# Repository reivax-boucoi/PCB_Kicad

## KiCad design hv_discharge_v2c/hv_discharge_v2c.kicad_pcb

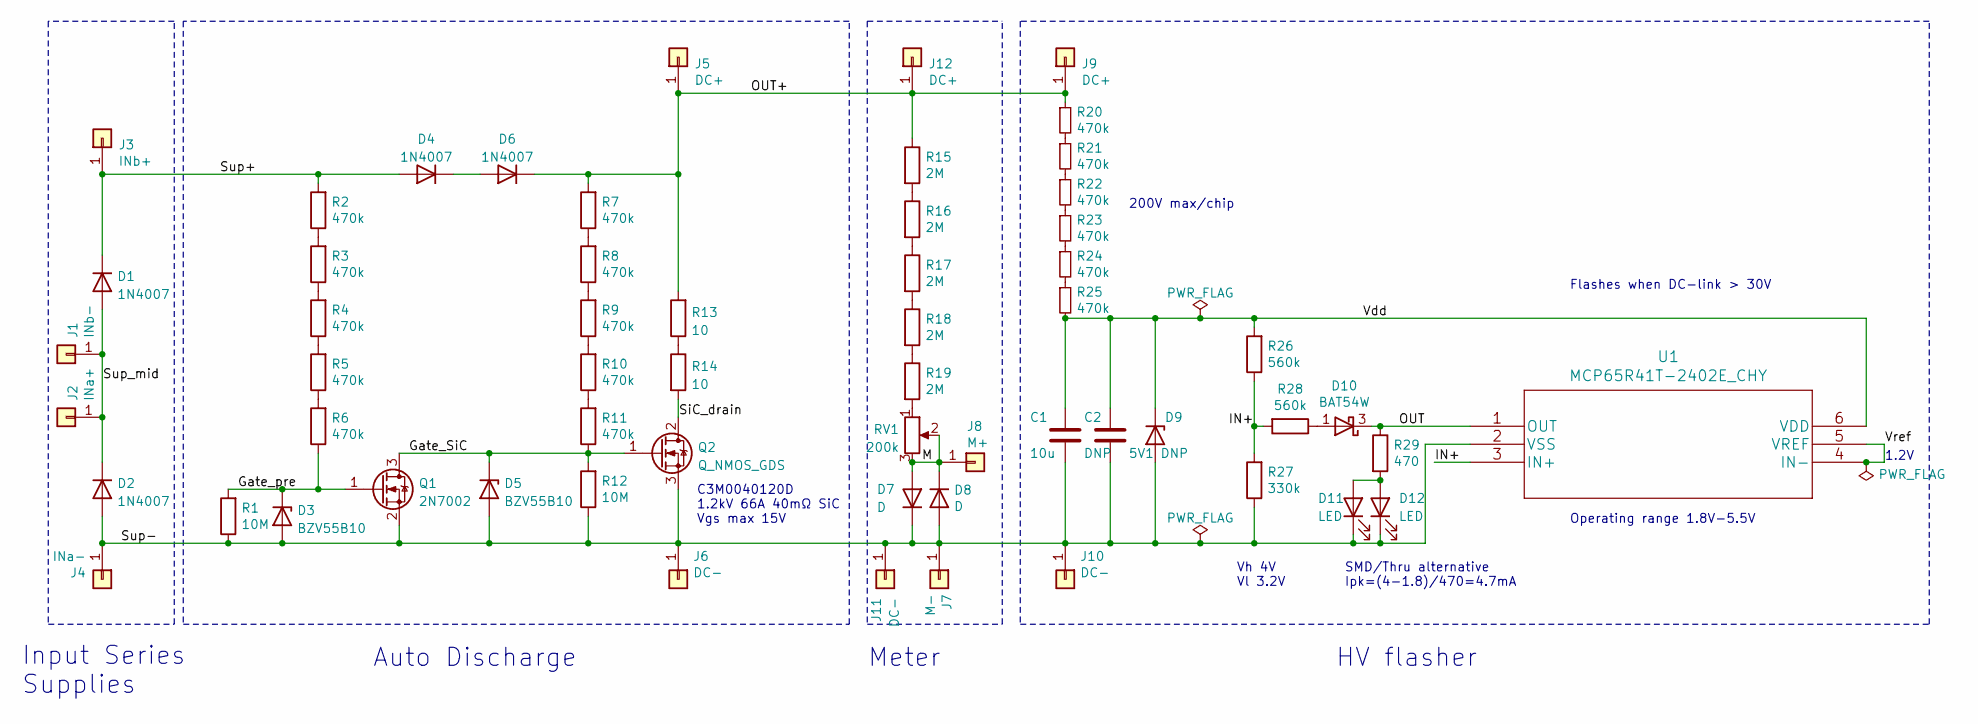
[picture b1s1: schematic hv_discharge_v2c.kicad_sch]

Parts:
C1: 10u; C_0805_2012Metric_Pad1.18x1.45mm_HandSolder
C2: DNP; C_0805_2012Metric_Pad1.18x1.45mm_HandSolder
D1, D2, D4, D6: 1N4007; D_DO-41_SOD81_P10.16mm_Horizontal
D3, D5: BZV55B10; D_MiniMELF
D7, D8: D; D_MiniMELF
D9: 5V1 DNP; D_MiniMELF
D10: BAT54W; SOT-23
D11: LED; LED_0805_2012Metric_Pad1.15x1.40mm_HandSolder
D12: LED; LED_D5.0mm
J1: INb-; TestPoint_THTPad_D2.5mm_Drill1.2mm
J2: INa+; TestPoint_THTPad_D2.5mm_Drill1.2mm
J3: INb+; TestPoint_THTPad_D2.5mm_Drill1.2mm
J4: INa-; TestPoint_THTPad_D2.5mm_Drill1.2mm
J5, J9, J12: DC+; TestPoint_THTPad_D2.5mm_Drill1.2mm
J6, J10, J11: DC-; TestPoint_THTPad_D2.5mm_Drill1.2mm
J7: M-; TestPoint_THTPad_D2.5mm_Drill1.2mm
J8: M+; TestPoint_THTPad_D2.5mm_Drill1.2mm
Q1: 2N7002; SOT-23
Q2: Q_NMOS_GDS; TO-247-3_Vertical
R1, R12: 10M; R_0805_2012Metric_Pad1.20x1.40mm_HandSolder
R2, R3, R4, R5, R6, R7, R8, R9, R10, R11, R20, R21, R22, R23, R24, R25: 470k; R_0805_2012Metric_Pad1.20x1.40mm_HandSolder
R13, R14: 10; THS2510RJ_special
R15, R16, R17, R18, R19: 2M; R_0805_2012Metric_Pad1.20x1.40mm_HandSolder
R26, R28: 560k; R_0805_2012Metric_Pad1.20x1.40mm_HandSolder
R27: 330k; R_0805_2012Metric_Pad1.20x1.40mm_HandSolder
R29: 470; R_0805_2012Metric_Pad1.20x1.40mm_HandSolder
RV1: 200k; Potentiometer_Bourns_3266Y_Vertical
U1: MCP65R41T-2402E_CHY; MCP65R41T-2402E

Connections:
/Gate_SiC: D5.1 (K), Q1.3 (D), Q2.1 (G), R11.1, R12.2
/Gate_pre: D3.1 (K), Q1.1 (G), R1.2, R6.1
/IN+: R26.1, R27.2, R28.2, U1.3 (IN+)
/M: D7.2 (A), D8.1 (K), J8.1, RV1.2, RV1.3
/OUT: D10.3 (K), R29.1, U1.1 (OUT)
/OUT+: D6.1 (K), J5.1, J9.1, J12.1, R7.2, R13.2, R15.1, R20.1
/SiC_drain: Q2.2 (D), R14.2
/Sup+: D1.1 (K), D4.2 (A), J3.1, R2.2
/Sup-: C1.2, C2.2, D2.2 (A), D3.2 (A), D5.2 (A), D7.1 (K), D8.2 (A), D9.2 (A), D11.1 (K), D12.1 (K), J4.1, J6.1, J7.1, J10.1, J11.1, Q1.2 (S), Q2.3 (S), R1.1, R12.1, R27.1, U1.2 (VSS)
/Sup_mid: D1.2 (A), D2.1 (K), J1.1, J2.1
/Vdd: C1.1, C2.1, D9.1 (K), R25.2, R26.2, U1.6 (VDD)
/Vref: U1.4 (IN-), U1.5 (VREF)
unnamed: D4.1 (K), D6.2 (A)
unnamed: D11.2 (A), D12.2 (A), R29.2
unnamed: R2.1, R3.2
unnamed: R3.1, R4.2
unnamed: R4.1, R5.2
unnamed: R5.1, R6.2
unnamed: R7.1, R8.2
unnamed: R8.1, R9.2
unnamed: R10.1, R11.2
unnamed: R9.1, R10.2
unnamed: R15.2, R16.1
unnamed: R16.2, R17.1
unnamed: R17.2, R18.1
unnamed: R18.2, R19.1
unnamed: R19.2, RV1.1
unnamed: R20.2, R21.1
unnamed: R21.2, R22.1
unnamed: R22.2, R23.1
unnamed: R23.2, R24.1
unnamed: R24.2, R25.1
unnamed: D10.1 (A), R28.1

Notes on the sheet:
Input Series Supplies
1.2V
Meter
Flashes when DC-link > 30V
SMD/Thru alternative Ipk=(4-1.8)/470=4.7mA
C3M0040120D 1.2kV 66A 40mΩ SiC Vgs max 15V
HV flasher
Auto Discharge
Operating range 1.8V-5.5V
Vh 4V Vl 3.2V
200V max/chip

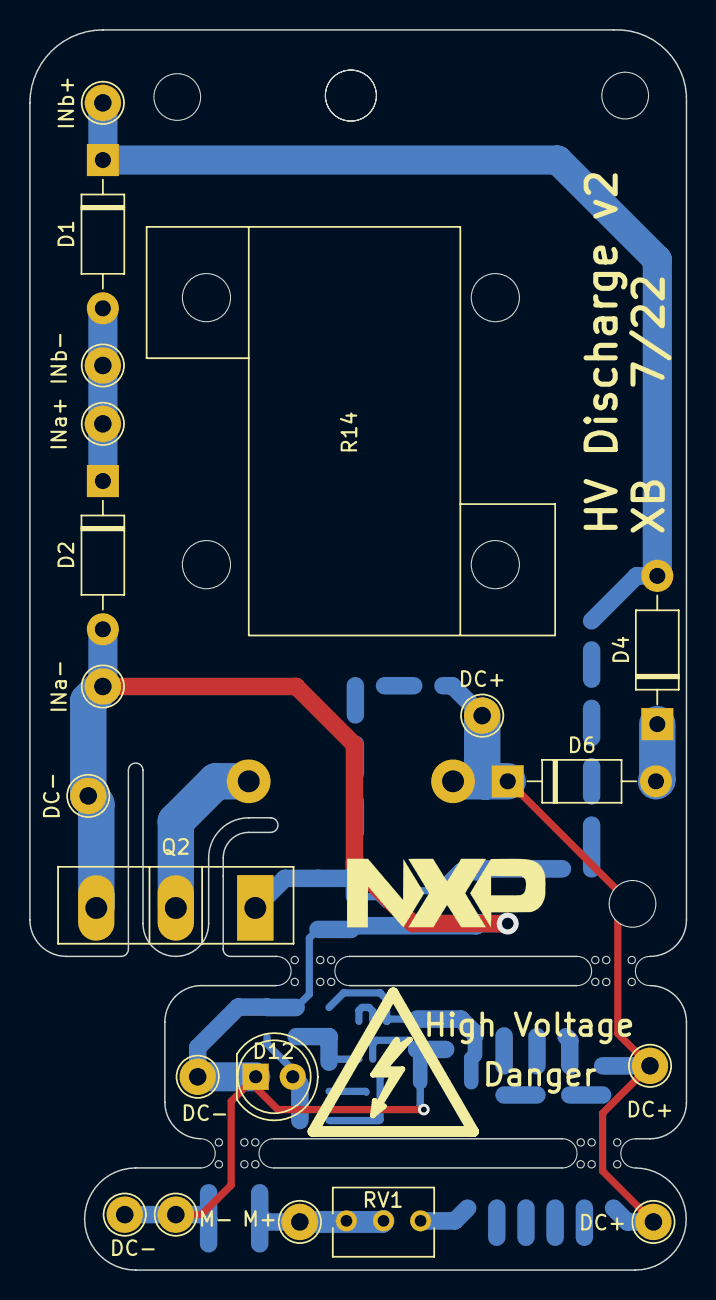
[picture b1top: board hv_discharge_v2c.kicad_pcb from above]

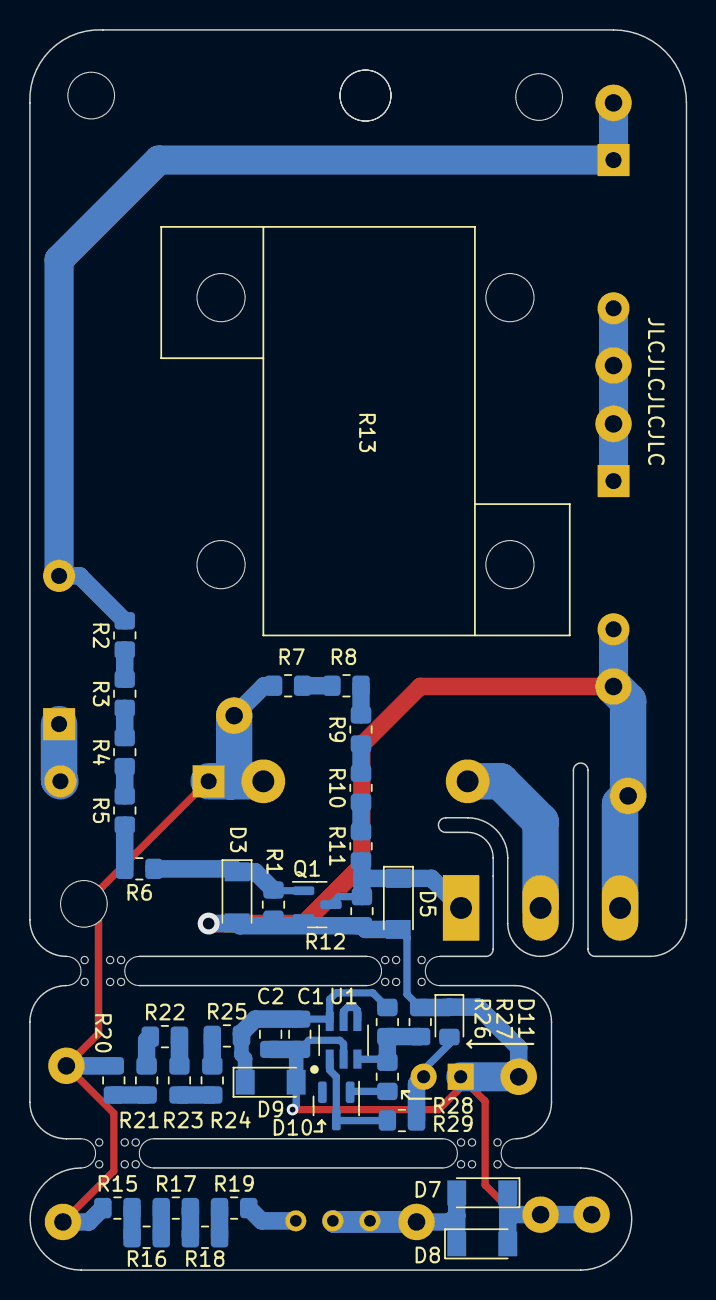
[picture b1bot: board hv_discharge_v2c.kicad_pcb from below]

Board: 2 copper layers, 45.0 x 85.0 mm, 63 parts (39 on the bottom side), 33 nets.

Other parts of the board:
mouse-bite-2mm-slot, mouse-bite-2mm-slot#2, mouse-bite-2mm-slot#3, mouse-bite-2mm-slot#4: VAL**; mouse-bite-2mm-slot

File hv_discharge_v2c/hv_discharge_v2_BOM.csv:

Reference,Value,Footprint,Datasheet,Qty,DNP
C1,10u,Capacitor_SMD:C_0805_2012Metric_Pad1.18x1.45mm_HandSolder,~,1,
C2,DNP,Capacitor_SMD:C_0805_2012Metric_Pad1.18x1.45mm_HandSolder,~,1,x
"D1,D2,D4,D6",1N4007,Diode_THT:D_DO-41_SOD81_P10.16mm_Horizontal,http://www.vishay.com/docs/88503/1n4001.pdf,4,"D1/D2 DNP, diode supplied replaces both D4/D6"
"D3,D5",BZV55B10,Diode_SMD:D_MiniMELF,https://assets.nexperia.com/documents/data-sheet/BZV55_SER.pdf,2,
"D7,D8",D,Diode_SMD:D_MiniMELF,~,2,x
D9,5V1,Diode_SMD:D_MiniMELF,~,1,
D10,BAT54W,Package_TO_SOT_SMD:SOT-23,https://assets.nexperia.com/documents/data-sheet/BAT54W_SER.pdf,1,
D11,LED,LED_SMD:LED_0805_2012Metric_Pad1.15x1.40mm_HandSolder,~,1,x
D12,LED,LED_THT:LED_D5.0mm,~,1,
J1,INb-,TestPoint:TestPoint_THTPad_D2.5mm_Drill1.2mm,~,1,x
J2,INa+,TestPoint:TestPoint_THTPad_D2.5mm_Drill1.2mm,~,1,x
J3,INb+,TestPoint:TestPoint_THTPad_D2.5mm_Drill1.2mm,~,1,x
J4,INa-,TestPoint:TestPoint_THTPad_D2.5mm_Drill1.2mm,~,1,x
"J5,J9,J12",DC+,TestPoint:TestPoint_THTPad_D2.5mm_Drill1.2mm,~,3,x
"J6,J10,J11",DC-,TestPoint:TestPoint_THTPad_D2.5mm_Drill1.2mm,~,3,x
J7,M-,TestPoint:TestPoint_THTPad_D2.5mm_Drill1.2mm,~,1,x
J8,M+,TestPoint:TestPoint_THTPad_D2.5mm_Drill1.2mm,~,1,x
Q1,2N7002,Package_TO_SOT_SMD:SOT-23,https://www.onsemi.com/pub/Collateral/NDS7002A-D.PDF,1,
Q2,Q_NMOS_GDS,Package_TO_SOT_THT:TO-247-3_Vertical,~,1,supplied
"R1,R12",10M,Resistor_SMD:R_0805_2012Metric_Pad1.20x1.40mm_HandSolder,~,2,
"R2,R3,R4,R5,R6,R7,R8,R9,R10,R11,R20,R21,R22,R23,R24,R25",470k,Resistor_SMD:R_0805_2012Metric_Pad1.20x1.40mm_HandSolder,~,16,
"R13,R14",10,footprints:THS2510RJ_special,~,2,supplied 47R
"R15,R16,R17,R18,R19",2M,Resistor_SMD:R_0805_2012Metric_Pad1.20x1.40mm_HandSolder,~,5,x
"R26,R28",560k,Resistor_SMD:R_0805_2012Metric_Pad1.20x1.40mm_HandSolder,~,2,
R27,330k,Resistor_SMD:R_0805_2012Metric_Pad1.20x1.40mm_HandSolder,~,1,
R29,470,Resistor_SMD:R_0805_2012Metric_Pad1.20x1.40mm_HandSolder,~,1,
RV1,200k,Potentiometer_THT:Potentiometer_Bourns_3266Y_Vertical,~,1,x
U1,MCP65R41T-2402E_CHY,footprints:MCP65R41T-2402E,,1,

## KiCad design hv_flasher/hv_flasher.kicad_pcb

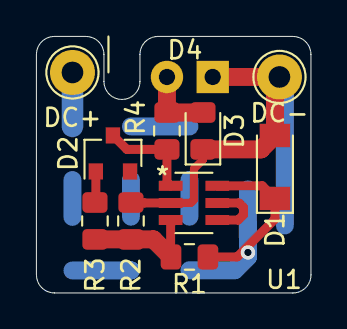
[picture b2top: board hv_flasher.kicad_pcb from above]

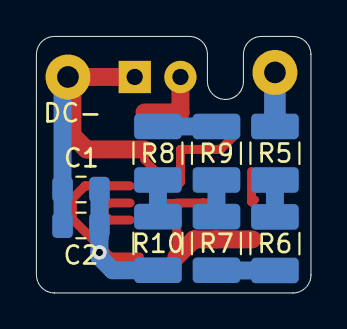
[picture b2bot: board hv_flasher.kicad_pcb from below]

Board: 2 copper layers, 15.2 x 14.2 mm, 19 parts (8 on the bottom side), 13 nets.

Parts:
C1, C2: 10u; C_0805_2012Metric_Pad1.15x1.40mm_HandSolder
D1: D_Zener; D_MiniMELF
D2: BAT54W; SOT-23
D3: LED; LED_0805_2012Metric_Pad1.15x1.40mm_HandSolder
D4: LED; LED_D5.0mm
DC+: DC+; TestPoint_THTPad_D2.5mm_Drill1.2mm
DC-: DC-; TestPoint_THTPad_D2.5mm_Drill1.2mm
R1, R2, R3: 100k; R_0805_2012Metric_Pad1.15x1.40mm_HandSolder
R4: 1k; R_0805_2012Metric_Pad1.15x1.40mm_HandSolder
R5, R6, R7, R8, R9, R10: 100k; R_1210_3225Metric_Pad1.42x2.65mm_HandSolder
U1: MCP65R41T-2402E_CHY; MCP65R41T-2402E

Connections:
/IN+: R1.1, R2.2, R3.2, U1.3
/OUT: D2.3, R4.1, U1.1
/Vdd: C1.1, C2.1, D1.1, R1.2, R10.2, U1.6
/Vref: U1.4, U1.5
/Vss: C1.2, C2.2, D1.2, D3.1, D4.1, DC-.1, R2.1, U1.2
unnamed: D2.1, R3.1
unnamed: D3.2, D4.2, R4.2
unnamed: DC+.1, R5.1
unnamed: R5.2, R6.1
unnamed: R6.2, R7.1
unnamed: R7.2, R8.1
unnamed: R8.2, R9.1
unnamed: R9.2, R10.1

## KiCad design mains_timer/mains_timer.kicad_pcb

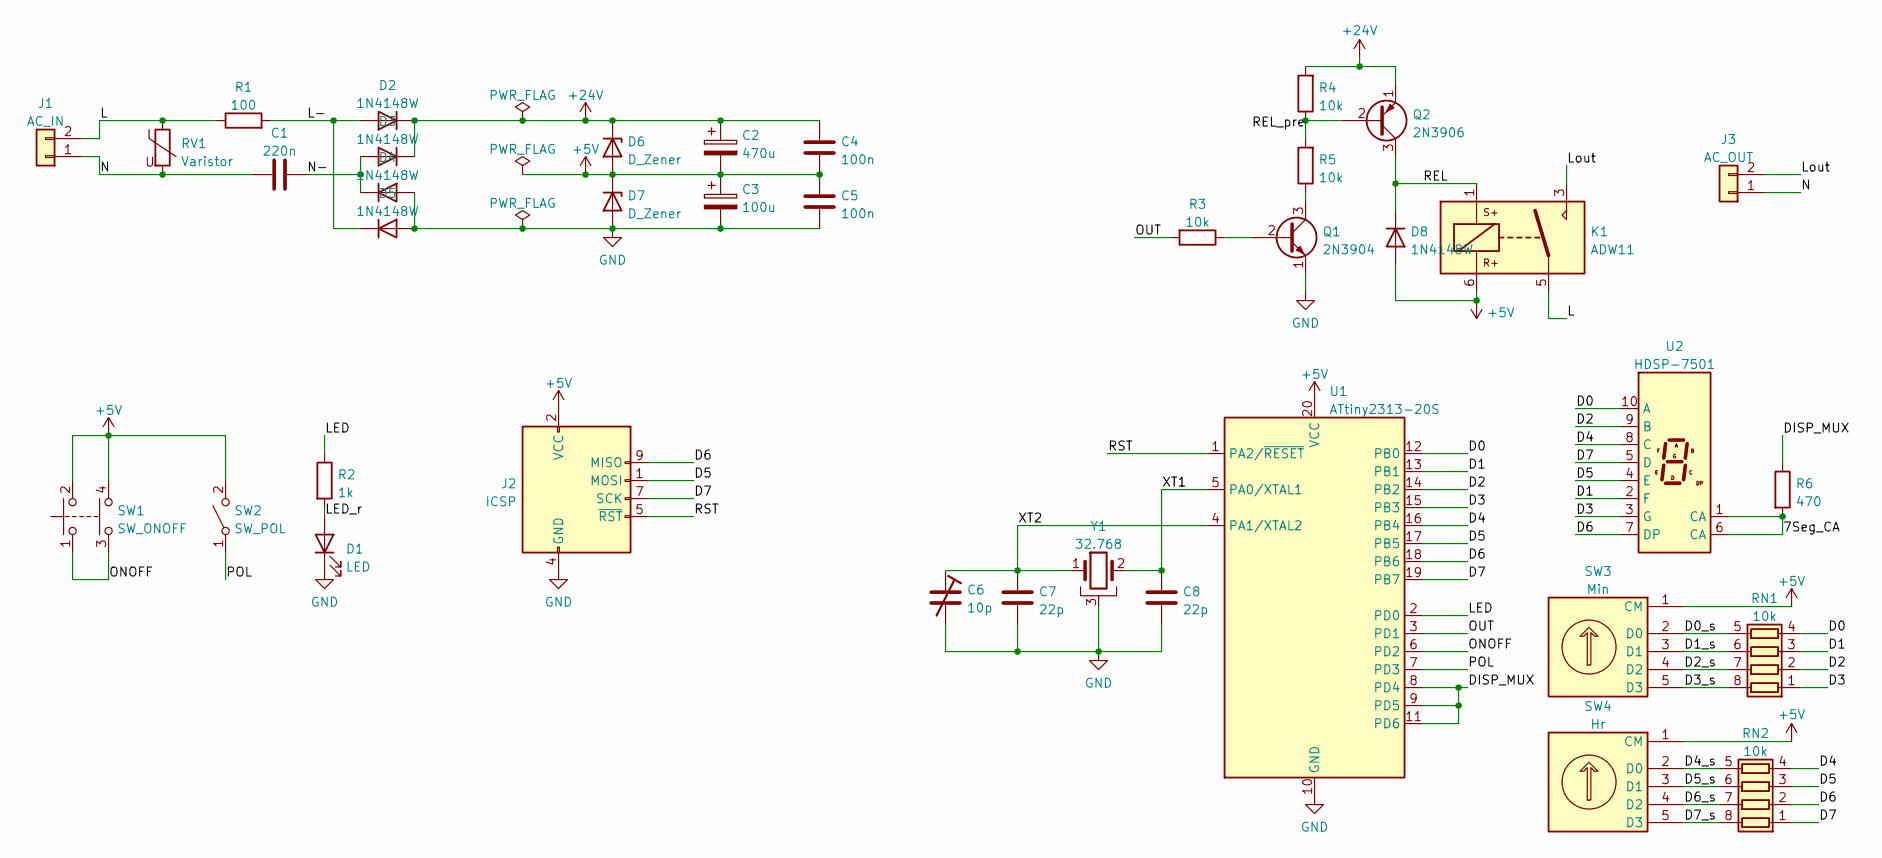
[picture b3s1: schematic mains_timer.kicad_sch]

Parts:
C1: 220n; C_Rect_L26.5mm_W8.5mm_P22.50mm_MKS4
C2: 470u; CP_Radial_D10.0mm_P2.50mm_P5.00mm
C3: 100u; CP_Radial_D7.5mm_P2.50mm
C4, C5: 100n; C_0603_1608Metric_Pad1.08x0.95mm_HandSolder
C6: 10p
C7, C8: 22p; C_0603_1608Metric_Pad1.08x0.95mm_HandSolder
D1: LED; LED_D5.0mm
D2, D3, D4, D5, D8: 1N4148W; D_SOD-123
D6: D_Zener; D_DO-15_P3.81mm_Vertical_AnodeUp
D7: D_Zener; D_MELF
J1: AC_IN; TerminalBlock_bornier-2_P5.08mm
J2: ICSP; PinHeader_2x05_P2.54mm_Vertical
J3: AC_OUT; TerminalBlock_bornier-2_P5.08mm
K1: ADW11; Relay_1P1T_NO_10x24x18.8mm_Panasonic_ADW11xxxxW_THT
Q1: 2N3904; TO-92_Inline
Q2: 2N3906; TO-92_Inline
R1: 100; R_Axial_DIN0309_L9.0mm_D3.2mm_P2.54mm_Vertical
R2: 1k; R_0603_1608Metric_Pad0.98x0.95mm_HandSolder
R3, R4, R5: 10k; R_0603_1608Metric_Pad0.98x0.95mm_HandSolder
R6: 470; R_0603_1608Metric_Pad0.98x0.95mm_HandSolder
RN1, RN2: 10k; R_Array_Concave_4x0603
RV1: Varistor; RV_Disc_D12mm_W4.6mm_P7.5mm
SW1: SW_ONOFF; Push_E-Switch_KS01Q01
SW2: SW_POL; PinHeader_1x02_P2.54mm_Vertical
SW3: Min; PinHeader_1x05_P2.54mm_Vertical
SW4: Hr; PinHeader_1x05_P2.54mm_Vertical
U1: ATtiny2313-20S; SOIC-20W_7.5x12.8mm_P1.27mm
U2: HDSP-7501; HDSP-A151
Y1: 32.768; Crystal_C38-LF_D3.0mm_L8.0mm_Horizontal_1EP_style2

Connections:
+5V: C2.2, C3.1, C4.2, C5.1, D6.2 (A), D7.1 (K), D8.2 (A), J2.2 (VCC), K1.6, SW1.2, SW1.4, SW2.2 (B), SW3.1 (CM), SW4.1 (CM), U1.20 (VCC)
+24V: C2.1, C4.1, D2.1 (K), D3.1 (K), D6.1 (K), Q2.1 (E), R4.2
/7Seg_CA: R6.2, U2.1 (CA), U2.6 (CA)
/D0: RN1.4 (R4.1), U1.12 (PB0), U2.10 (A)
/D0_s: RN1.5 (R4.2), SW3.2 (D0)
/D1: RN1.3 (R3.1), U1.13 (PB1), U2.2 (F)
/D1_s: RN1.6 (R3.2), SW3.3 (D1)
/D2: RN1.2 (R2.1), U1.14 (PB2), U2.9 (B)
/D2_s: RN1.7 (R2.2), SW3.4 (D2)
/D3: RN1.1 (R1.1), U1.15 (PB3), U2.3 (G)
/D3_s: RN1.8 (R1.2), SW3.5 (D3)
/D4: RN2.4 (R4.1), U1.16 (PB4), U2.8 (C)
/D4_s: RN2.5 (R4.2), SW4.2 (D0)
/D5: J2.1 (MOSI), RN2.3 (R3.1), U1.17 (PB5), U2.4 (E)
/D5_s: RN2.6 (R3.2), SW4.3 (D1)
/D6: J2.9 (MISO), RN2.2 (R2.1), U1.18 (PB6), U2.7 (DP)
/D6_s: RN2.7 (R2.2), SW4.4 (D2)
/D7: J2.7 (SCK), RN2.1 (R1.1), U1.19 (PB7), U2.5 (D)
/D7_s: RN2.8 (R1.2), SW4.5 (D3)
/DISP_MUX: R6.1, U1.8 (PD4), U1.9 (PD5), U1.11 (PD6)
/L: J1.2, K1.5, R1.1, RV1.1
/L-: D2.2 (A), D5.1 (K), R1.2
/LED: R2.1, U1.2 (PD0)
/LED_r: D1.2 (A), R2.2
/Lout: J3.2, K1.3
/N: C1.1, J1.1, J3.1, RV1.2
/N-: C1.2, D3.2 (A), D4.1 (K)
/ONOFF: SW1.1, SW1.3, U1.6 (PD2)
/OUT: R3.2, U1.3 (PD1)
/POL: SW2.1 (A), U1.7 (PD3)
/REL: D8.1 (K), K1.1, Q2.3 (C)
/REL_pre: Q2.2 (B), R4.1, R5.2
/RST: J2.5 (~RST), U1.1 (PA2/~RESET)
/XT1: C8.1, U1.5 (PA0/XTAL1), Y1.2
/XT2: C6.1, C7.1, U1.4 (PA1/XTAL2), Y1.1
GND: C3.2, C5.2, C6.2, C7.2, C8.2, D1.1 (K), D4.2 (A), D5.2 (A), D7.2 (A), J2.4 (GND), J2.6 (GND), J2.8 (GND), J2.10 (GND), Q1.1 (E), U1.10 (GND), Y1.3
unnamed: Q1.2 (B), R3.1
unnamed: Q1.3 (C), R5.1

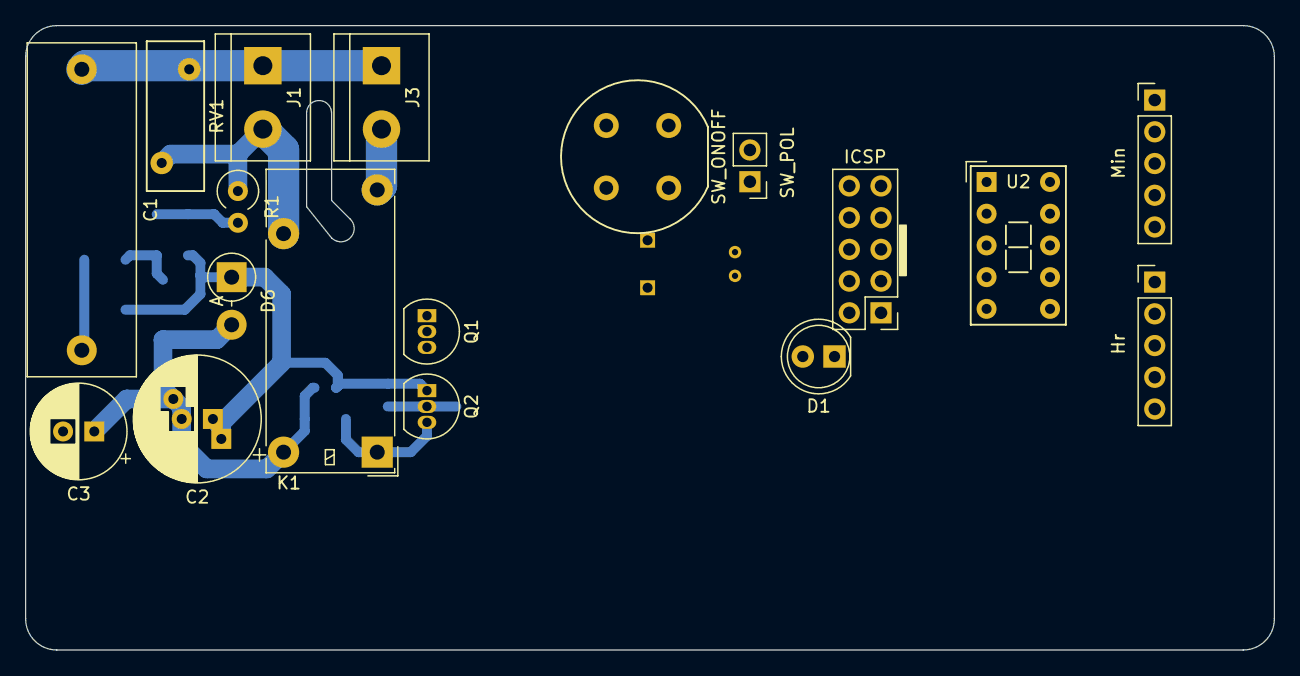
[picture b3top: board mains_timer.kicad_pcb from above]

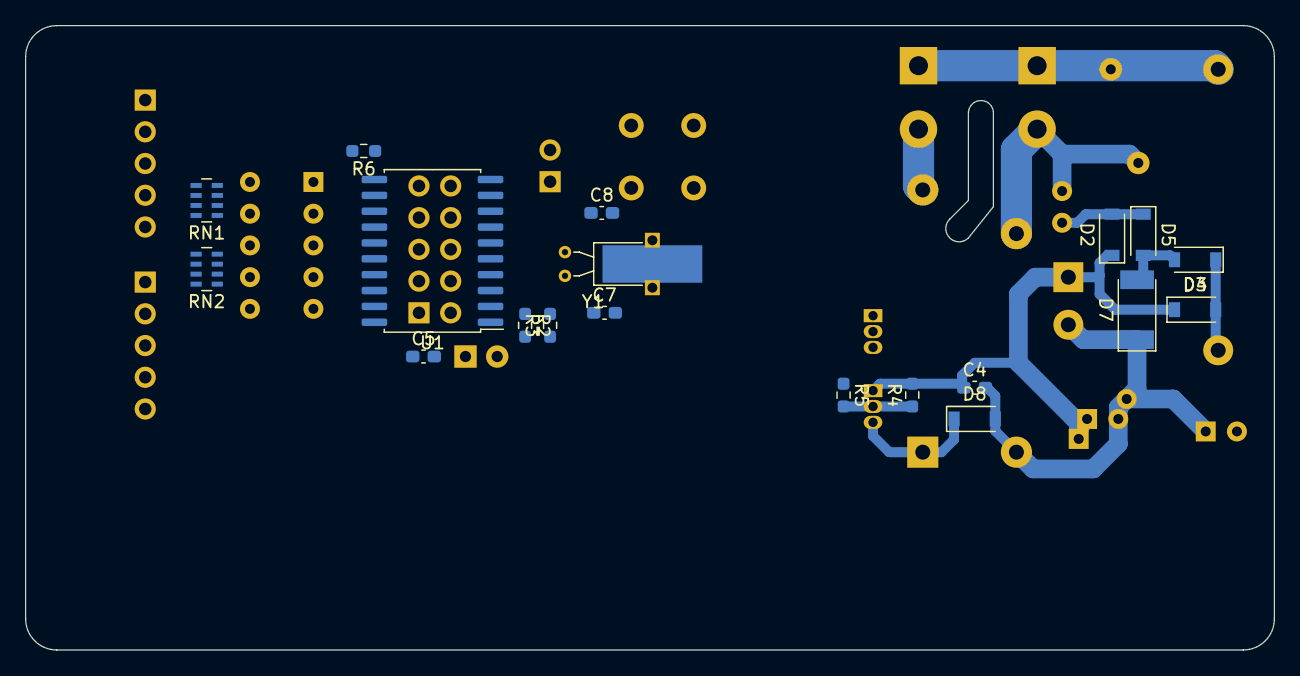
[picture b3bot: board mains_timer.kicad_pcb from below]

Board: 2 copper layers, 100.0 x 50.0 mm, 37 parts (19 on the bottom side), 38 nets.

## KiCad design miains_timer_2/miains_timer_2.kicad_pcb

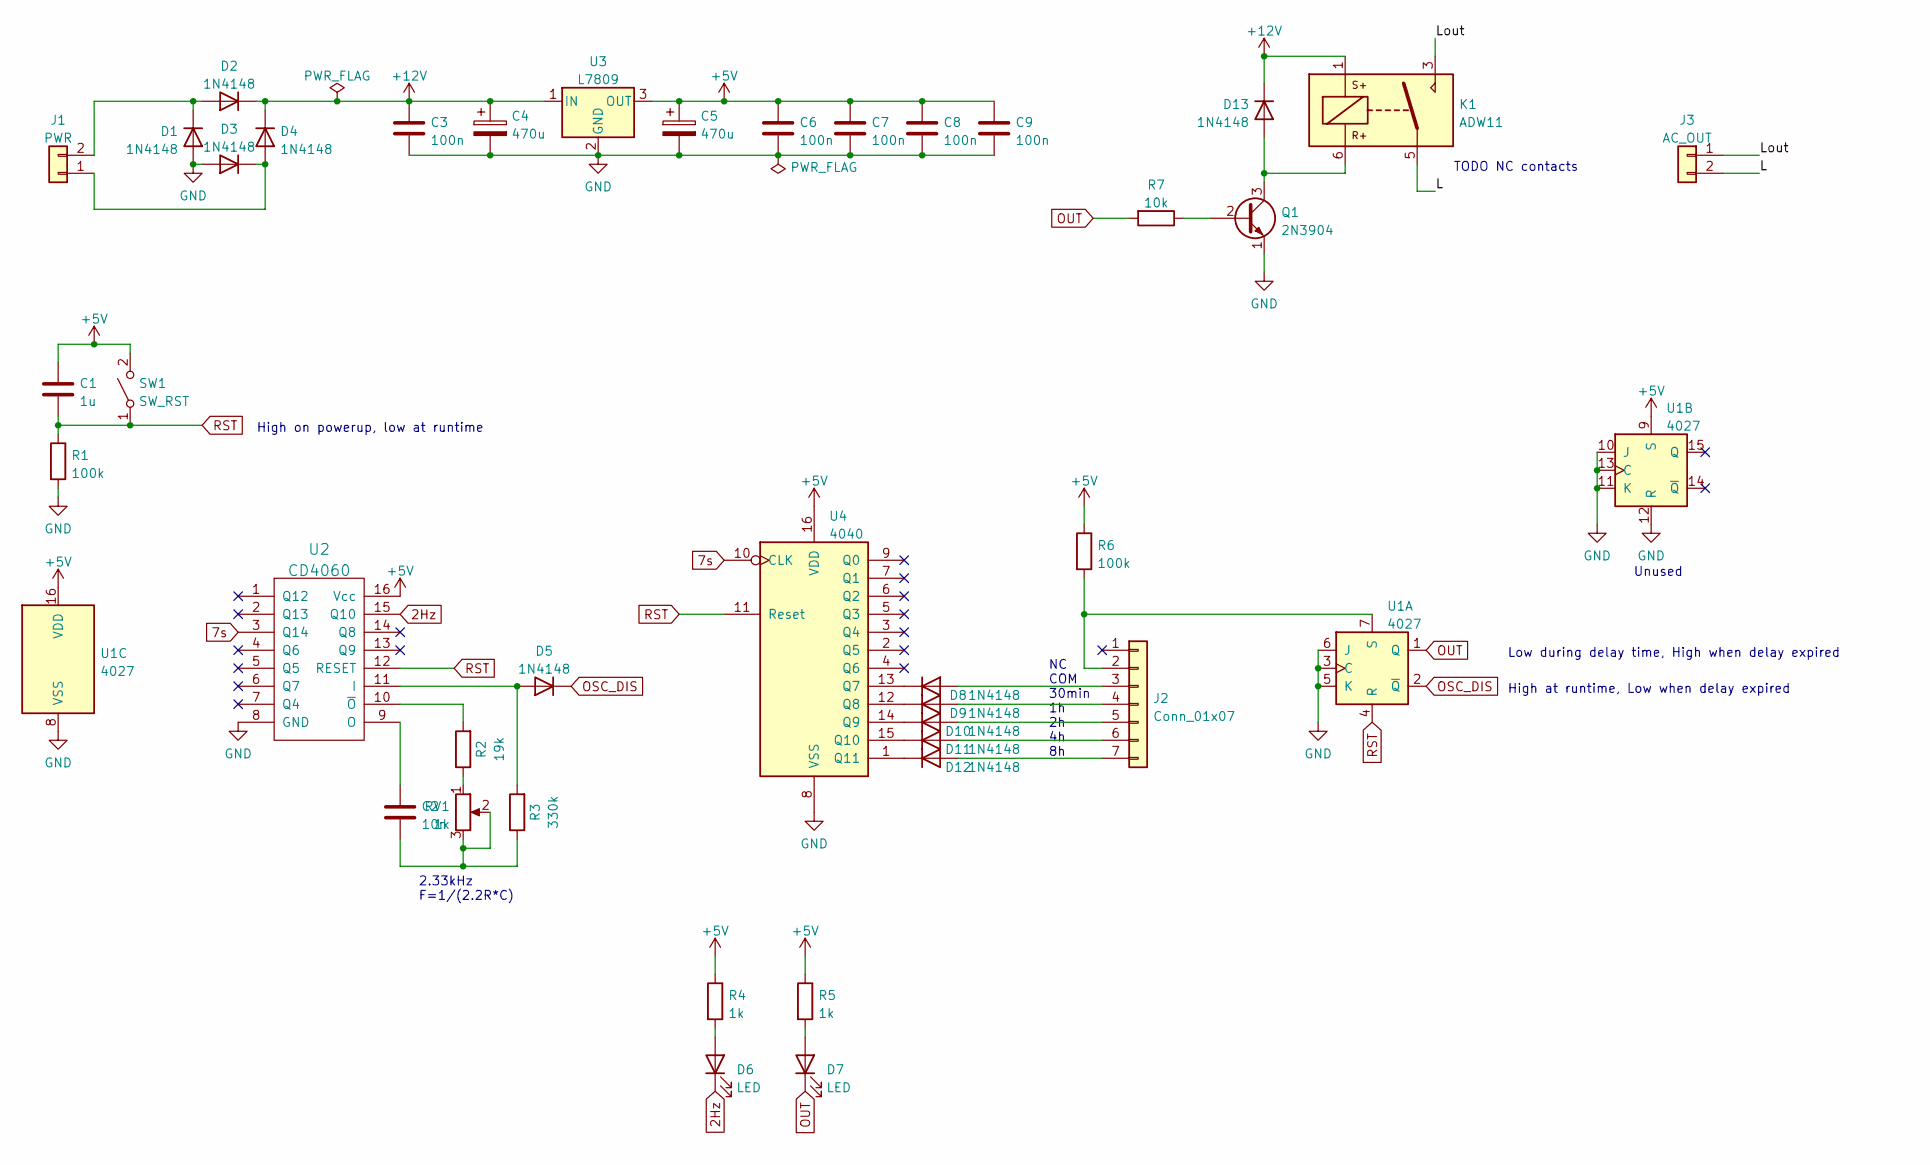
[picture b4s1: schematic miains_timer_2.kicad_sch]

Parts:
C1: 1u; C_0805_2012Metric_Pad1.18x1.45mm_HandSolder
C2: 10n; C_0805_2012Metric_Pad1.18x1.45mm_HandSolder
C3, C6, C7, C8, C9: 100n; C_0805_2012Metric_Pad1.18x1.45mm_HandSolder
C4, C5: 470u; CP_Radial_D8.0mm_P2.50mm
D1, D2, D3, D4, D5, D8, D9, D10, D11, D12, D13: 1N4148; D_MiniMELF
D6, D7: LED; LED_D5.0mm
J1: PWR; TerminalBlock_bornier-2_P5.08mm
J2: Conn_01x07; PinSocket_1x07_P2.54mm_Vertical
J3: AC_OUT; TerminalBlock_bornier-2_P5.08mm
K1: ADW11; Relay_1P1T_NO_10x24x18.8mm_Panasonic_ADW11xxxxW_THT
Q1: 2N3904; TO-92_Inline
R1, R6: 100k; R_0805_2012Metric_Pad1.20x1.40mm_HandSolder
R2: 19k; R_0805_2012Metric_Pad1.20x1.40mm_HandSolder
R3: 330k; R_0805_2012Metric_Pad1.20x1.40mm_HandSolder
R4, R5: 1k; R_0805_2012Metric_Pad1.20x1.40mm_HandSolder
R7: 10k; R_0805_2012Metric_Pad1.20x1.40mm_HandSolder
RV1: 1k; Potentiometer_Bourns_3386X_Horizontal
SW1: SW_RST; PinHeader_1x02_P2.54mm_Vertical
U1: 4027; DIP-16_W7.62mm_Socket_LongPads
U2: CD4060; DIP-16_W7.62mm_Socket_LongPads
U3: L7809; TO-220-3_Vertical
U4: 4040; DIP-16_W7.62mm_Socket_LongPads

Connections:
2Hz: D6.1 (K), U2.15 (Q10)
7s: U2.3 (Q14), U4.10 (CLK)
+5V: C1.1, C5.1, C6.1, C7.1, C8.1, C9.1, R4.1, R5.1, R6.1, SW1.2 (B), U1.9 (S), U1.16 (VDD), U2.16 (Vcc), U3.3 (OUT), U4.16 (VDD)
+12V: C3.1, C4.1, D2.1 (K), D4.1 (K), D13.1 (K), K1.1, U3.1 (IN)
/L: J3.2, K1.5
/Lout: J3.1, K1.3
GND: C3.2, C4.2, C5.2, C6.2, C7.2, C8.2, C9.2, D1.2 (A), D3.2 (A), Q1.1 (E), R1.2, U1.3 (C), U1.5 (K), U1.6 (J), U1.8 (VSS), U1.10 (J), U1.11 (K), U1.12 (R), U1.13 (C), U2.8 (GND), U3.2 (GND), U4.8 (VSS)
unnamed: C2.1, U2.9 (O)
unnamed: C2.2, R3.1, RV1.2, RV1.3
unnamed: D1.1 (K), D2.2 (A), J1.2
unnamed: D3.1 (K), D4.2 (A), J1.1
unnamed: D5.2 (A), R3.2, U2.11 (I)
unnamed: D6.2 (A), R4.2
unnamed: D7.2 (A), R5.2
unnamed: D8.1 (K), U4.13 (Q7)
unnamed: D8.2 (A), J2.3
unnamed: D9.1 (K), U4.12 (Q8)
unnamed: D9.2 (A), J2.4
unnamed: D10.1 (K), U4.14 (Q9)
unnamed: D10.2 (A), J2.5
unnamed: D11.1 (K), U4.15 (Q10)
unnamed: D11.2 (A), J2.6
unnamed: D12.1 (K), U4.1 (Q11)
unnamed: D12.2 (A), J2.7
unnamed: J2.2, R6.2, U1.7 (S)
unnamed: D13.2 (A), K1.6, Q1.3 (C)
unnamed: Q1.2 (B), R7.1
unnamed: R2.1, RV1.1
unnamed: R2.2, U2.10 (~O)
OSC_DIS: D5.1 (K), U1.2 (~Q)
OUT: D7.1 (K), R7.2, U1.1 (Q)
RST: C1.2, R1.1, SW1.1 (A), U1.4 (R), U2.12 (RESET), U4.11 (Reset)

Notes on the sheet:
High at runtime, Low when delay expired
Unused
Low during delay time, High when delay expired
High on powerup, low at runtime
NC COM 30min 1h 2h 4h 8h
TODO NC contacts
2.33kHz F=1/(2.2R*C)

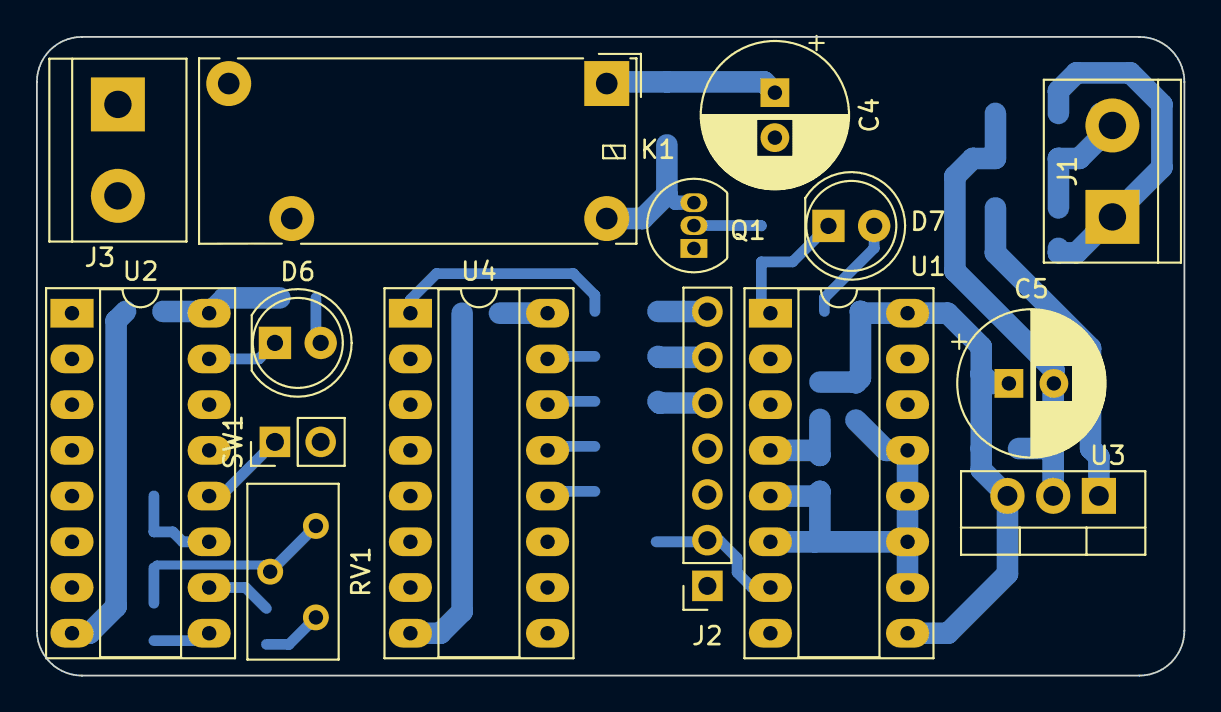
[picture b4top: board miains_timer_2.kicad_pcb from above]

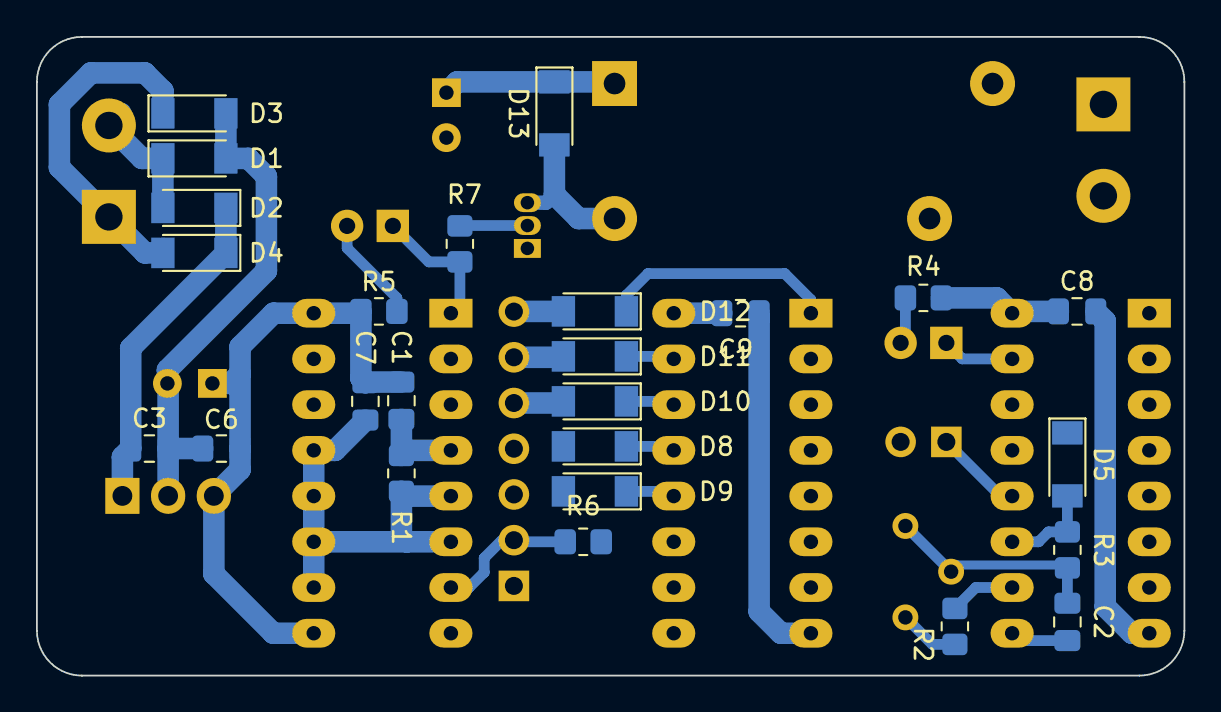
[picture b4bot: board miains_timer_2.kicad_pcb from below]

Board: 2 copper layers, 63.8 x 35.5 mm, 40 parts (25 on the bottom side), 32 nets.

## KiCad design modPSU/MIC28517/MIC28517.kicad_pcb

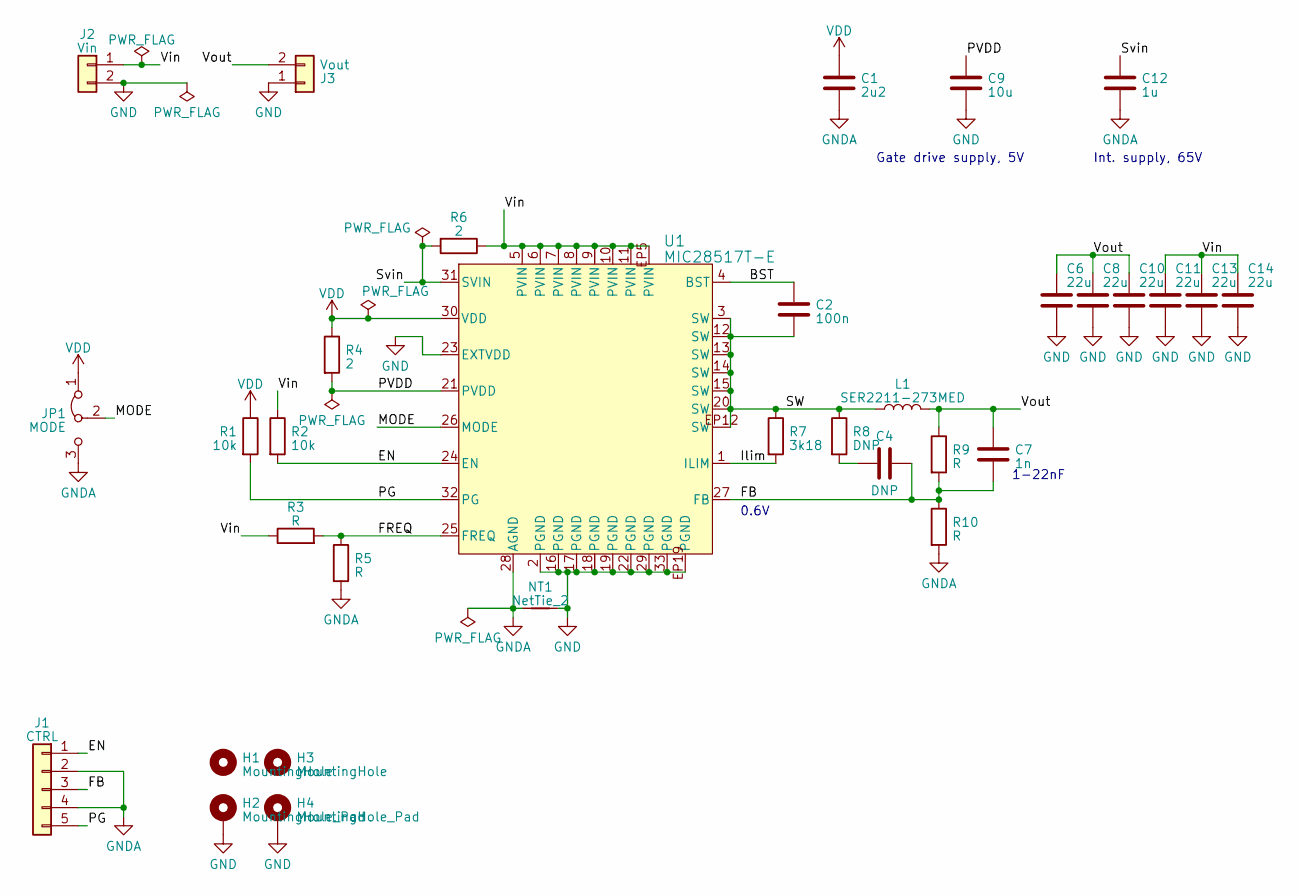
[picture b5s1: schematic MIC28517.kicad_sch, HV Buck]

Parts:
C1: 2u2; C_0805_2012Metric; Voltage 10
C2: 100n; C_0603_1608Metric; Voltage 100
C4: DNP; C_0603_1608Metric; Voltage 100
C6, C8, C10, C11, C13, C14: 22u; C_2220_5650Metric; Voltage 100
C7: 1n; C_0603_1608Metric; Voltage 100
C9: 10u; C_0805_2012Metric; Voltage 10
C12: 1u; C_0805_2012Metric; Voltage 100
H1, H3: MountingHole; MountingHole_4.3mm_M4
H2, H4: MountingHole_Pad; MountingHole_4.3mm_M4_Pad_Via
J1: CTRL; PinSocket_1x05_P2.54mm_Horizontal
J2: Vin; TerminalBlock_bornier-2_P5.08mm
J3: Vout; TerminalBlock_bornier-2_P5.08mm
JP1: MODE; SolderJumper-3_P1.3mm_Bridged12_RoundedPad1.0x1.5mm
L1: SER2211-273MED; SER2211_shielded_flatwire_L; Voltage 27u
NT1: NetTie_2; NetTie-2_SMD_Pad0.2mm
R1, R2: 10k; R_0603_1608Metric
R3, R5, R9, R10: R; R_0603_1608Metric
R4, R6: 2; R_0805_2012Metric
R7: 3k18; R_0603_1608Metric
R8: DNP; R_0603_1608Metric
U1: MIC28517T-E; MIC28517_VQFN32_EP_Lversion

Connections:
/BST: C2.1, U1.4 (BST)
/EN: J1.1, R2.2, U1.24 (EN)
/FB: C4.2, C7.2, J1.3, R9.2, R10.1, U1.27 (FB)
/FREQ: R3.2, R5.1, U1.25 (FREQ)
/Ilim: R7.2, U1.1 (ILIM)
/MODE: JP1.2 (C), U1.26 (MODE)
/PG: J1.5, R1.2, U1.32 (PG)
/PVDD: C9.1, R4.2, U1.21 (PVDD)
/SW: C2.2, L1.2, R7.1, R8.1, U1.3 (SW), U1.12 (SW), U1.13 (SW), U1.14 (SW), U1.15 (SW), U1.20 (SW), U1.EP12 (SW)
/Svin: C12.1, R6.2, U1.31 (SVIN)
/Vin: C11.1, C13.1, C14.1, J2.1, R2.1, R3.1, R6.1, U1.5 (PVIN), U1.6 (PVIN), U1.7 (PVIN), U1.8 (PVIN), U1.9 (PVIN), U1.10 (PVIN), U1.11 (PVIN), U1.EP5 (PVIN)
/Vout: C6.1, C7.1, C8.1, C10.1, J3.2, L1.1, R9.1
GND: C6.2, C8.2, C9.2, C10.2, C11.2, C13.2, C14.2, H2.1, H4.1, J2.2, J3.1, NT1.2, U1.2 (PGND), U1.16 (PGND), U1.17 (PGND), U1.18 (PGND), U1.19 (PGND), U1.22 (PGND), U1.23 (EXTVDD), U1.29 (PGND), U1.33 (PGND), U1.EP19 (PGND)
GNDA: C1.2, C12.2, J1.2, J1.4, JP1.3 (B), NT1.1, R5.2, R10.2, U1.28 (AGND)
unnamed: C4.1, R8.2
VDD: C1.1, JP1.1 (A), R1.1, R4.1, U1.30 (VDD)

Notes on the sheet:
Int. supply, 65V
0.6V
1-22nF
Gate drive supply, 5V

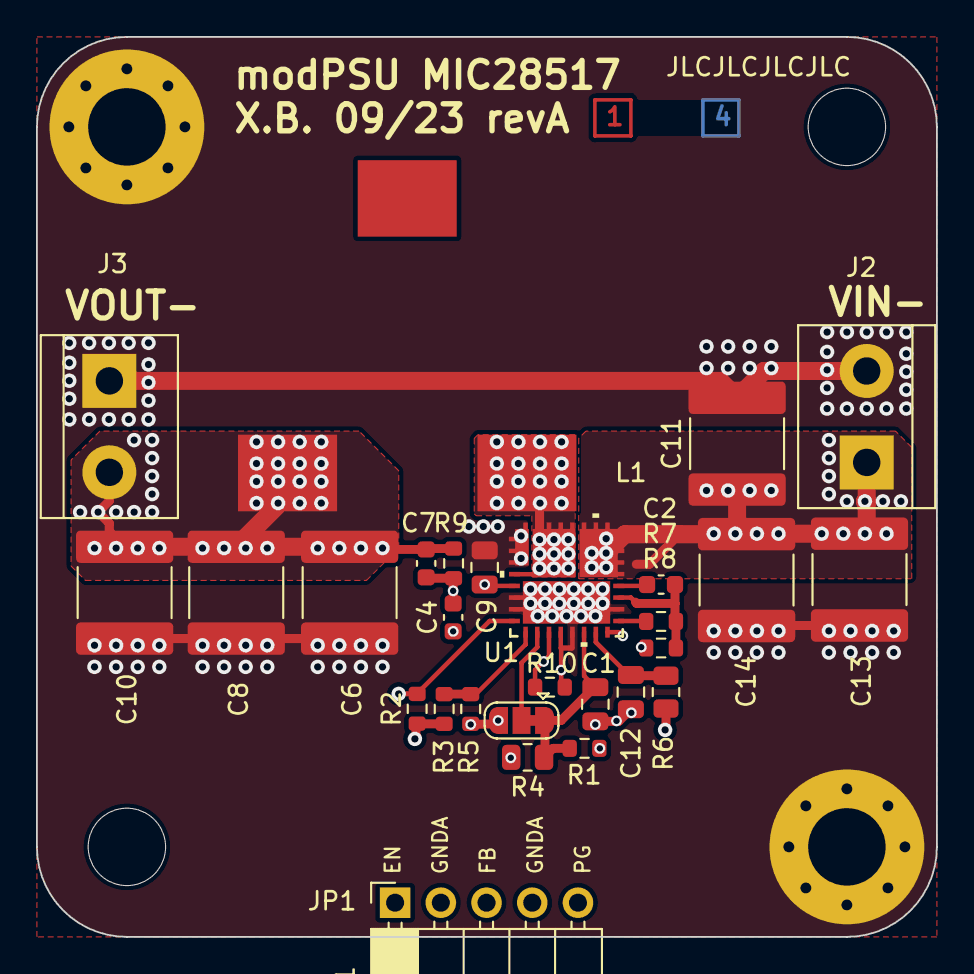
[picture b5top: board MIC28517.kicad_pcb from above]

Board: 4 copper layers, 50.0 x 50.0 mm, 33 parts (0 on the bottom side), 16 nets.

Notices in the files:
parts and their libraries:
Copyright 2021 Accelerated Designs. All rights reserved.
